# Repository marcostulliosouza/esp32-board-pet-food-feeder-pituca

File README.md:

# ESP32 Pet Food Feeder – Pituca

<div align="center">

</div>

Placa eletrônica baseada no ESP32 desenvolvida para um alimentador automático de pets, permitindo controle preciso de horários e porções de ração, com possibilidade de integração via Wi-Fi.

## Visão geral

Este projeto foi criado para automatizar a alimentação de animais domésticos de forma confiável e prática. A placa utiliza um módulo ESP32 encaixado via headers (socket), facilitando montagem, manutenção e substituição do microcontrolador.

## Funcionalidades

*  Programação de horários de alimentação
*  Conectividade Wi-Fi (ESP32)
*  Alimentação externa regulada
*  Interface para periféricos (motores, sensores, etc.)
*  Design modular com ESP32 removível

##  Hardware

* ESP32 DevKit (via socket)
* Conectores para expansão (GPIOs)
* Trilhas dimensionadas para alimentação e sinais
* Plano de GND em múltiplas camadas

##  Status do projeto

Em desenvolvimento

##  Imagens

## Autor

Projeto desenvolvido por **Marcos Tullio Silva de Souza**

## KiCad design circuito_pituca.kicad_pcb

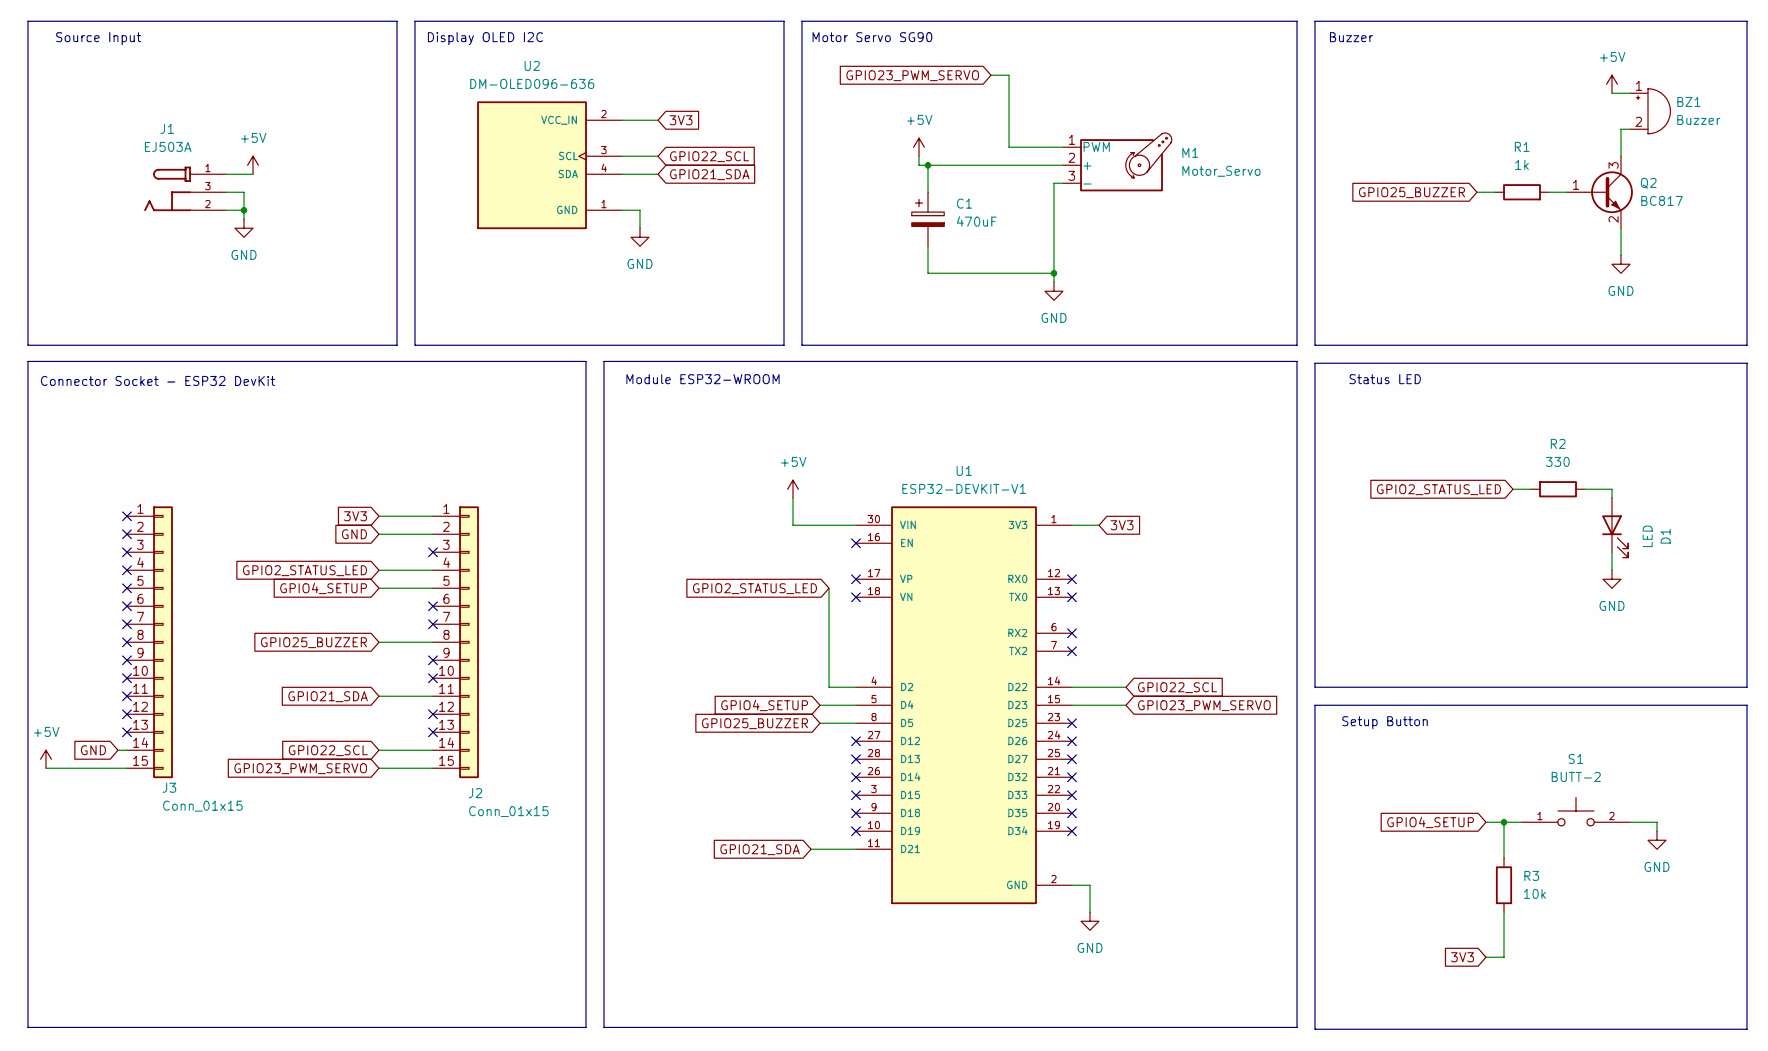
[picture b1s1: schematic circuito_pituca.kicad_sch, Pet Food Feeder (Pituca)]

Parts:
BZ1: Buzzer; Buzzer_12x9.5RM7.6
C1: 470uF; CP_Elec_6.3x7.7
D1: LED; LED_0805_2012Metric_Pad1.15x1.40mm_HandSolder
J1: EJ503A; MPD_EJ503A; PARTREV B
J2, J3: Conn_01x15; PinSocket_1x15_P2.54mm_Vertical
M1: Motor_Servo; PinHeader_1x03_P2.54mm_Horizontal
Q2: BC817; SOT-23
R1: 1k; R_0805_2012Metric
R2: 330; R_0805_2012Metric
R3: 10k; R_0805_2012Metric
S1: BUTT-2; SW_BUTT-2; PARTREV N/A
U1: ESP32-DEVKIT-V1; MODULE_ESP32_DEVKIT_V1; PARTREV N/A
U2: DM-OLED096-636; MODULE_DM-OLED096-636; PARTREV 2018-09-10

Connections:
3V3: J2.1, R3.2, U1.1 (3V3), U2.2 (VCC_IN)
+5V: BZ1.1 (+), C1.1, J1.1, J3.15, M1.2 (+), U1.30 (VIN)
GND: C1.2, D1.1 (K), J1.2, J1.3, J2.2, J3.14, M1.3 (-), Q2.2 (E), S1.2, U1.2 (GND), U1.29 (GND), U2.1 (GND)
GPIO2_STATUS_LED: J2.4, R2.2, U1.4 (D2)
GPIO4_SETUP: J2.5, R3.1, S1.1, U1.5 (D4)
GPIO21_SDA: J2.11, U1.11 (D21), U2.4 (SDA)
GPIO22_SCL: J2.14, U1.14 (D22), U2.3 (SCL)
GPIO23_PWM_SERVO: J2.15, M1.1 (PWM), U1.15 (D23)
GPIO25_BUZZER: J2.8, R1.1, U1.8 (D5)
unnamed: BZ1.2 (-), Q2.3 (C)
unnamed: D1.2 (A), R2.1
unnamed: Q2.1 (B), R1.2

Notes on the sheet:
Status LED
Setup Button
Connector Socket - ESP32 DevKit
Display OLED I2C
Source Input
Buzzer
Motor Servo SG90
Module ESP32-WROOM

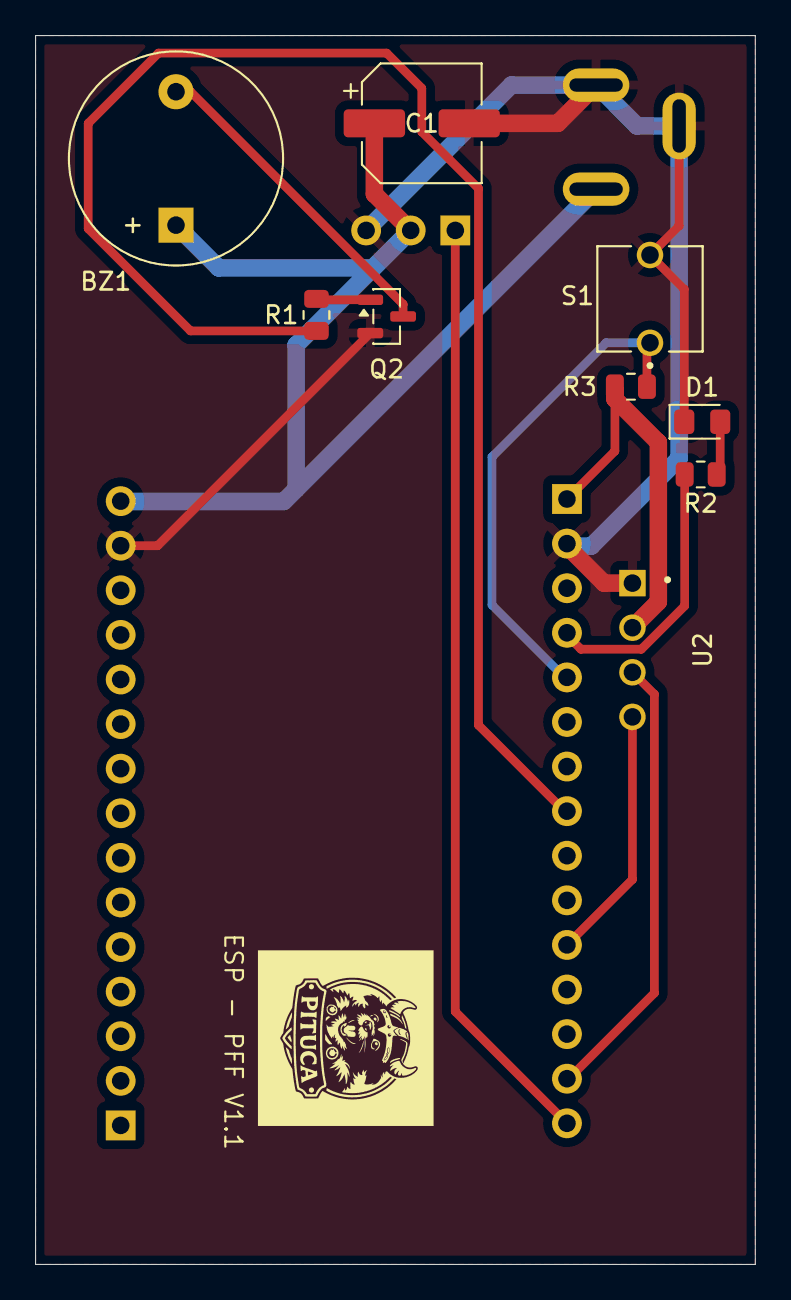
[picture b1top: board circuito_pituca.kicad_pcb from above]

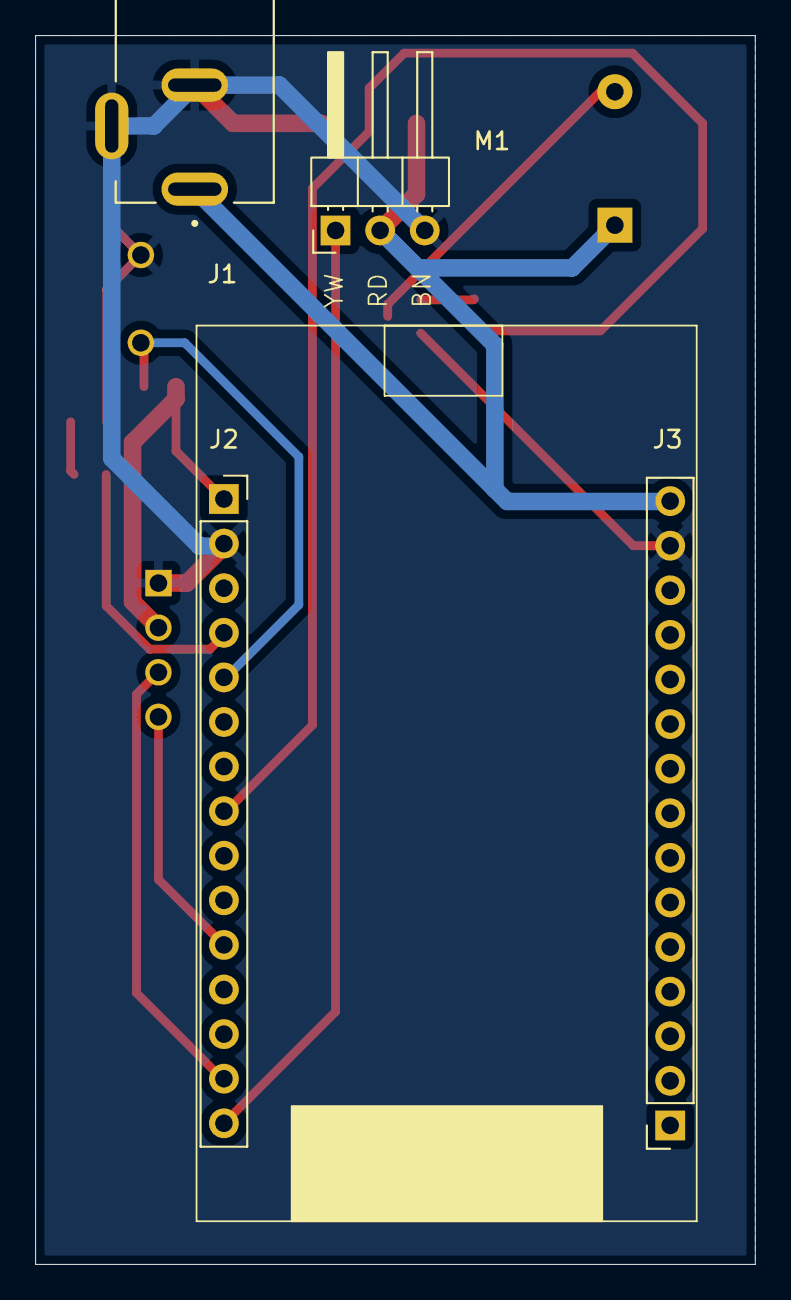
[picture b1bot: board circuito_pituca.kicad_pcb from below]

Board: 2 copper layers, 41.0 x 70.0 mm, 14 parts (4 on the bottom side), 12 nets.

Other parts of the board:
Logo: LOGO; silk_logo_pituca

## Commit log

2026-03-19 Update README with project details and features
    Added project overview, features, hardware details, and author information.
2026-03-19 primeira versão
2026-03-19 adicionado logo
2026-03-19 Update README with images and project details
    Added images and updated project description.
2026-03-19 Add project title to README
    Added project title to README for clarity.
